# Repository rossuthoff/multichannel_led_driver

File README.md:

# multichannel_led_driver
Switching boost LED driver based on the Linear Technology [LT3478-1](http://www.analog.com/en/products/power-management/led-driver-ic/buck-boost-led-drivers/lt3478.html) chip.

## related repositories
This design requires the footprints found in the [kicad_footprints](https://github.com/rossuthoff/kicad_footprints) repository. Make sure the library and .mod files are added to your folder search locations. This board utilizes the [ytai/IOIO](https://github.com/ytai/ioio) microcontroller (MCU) and is designed to match to its header layout. Other microcontrollers that can send 3.3 V signals and control an I2C interface may be used. 

## general use
### power supply
LED driver is used in boost mode. The battery voltage must be less than the voltage drop across each individual LED string. Header connnection between this board and the IOIO board provide power to the MCU.

### led strings
Connect the LED strings to V+ (anode) and V1 through V9 (cathodes) connections. The LED string to be illuminated is controlled through a 3.3V signal to the s1 through s9 pins. The applied current is controlled through a Analog Devices [AD5247](http://www.analog.com/en/products/digital-to-analog-converters/digital-potentiometers/ad5247.html) digital potentiometer with an I2C interface.

# references

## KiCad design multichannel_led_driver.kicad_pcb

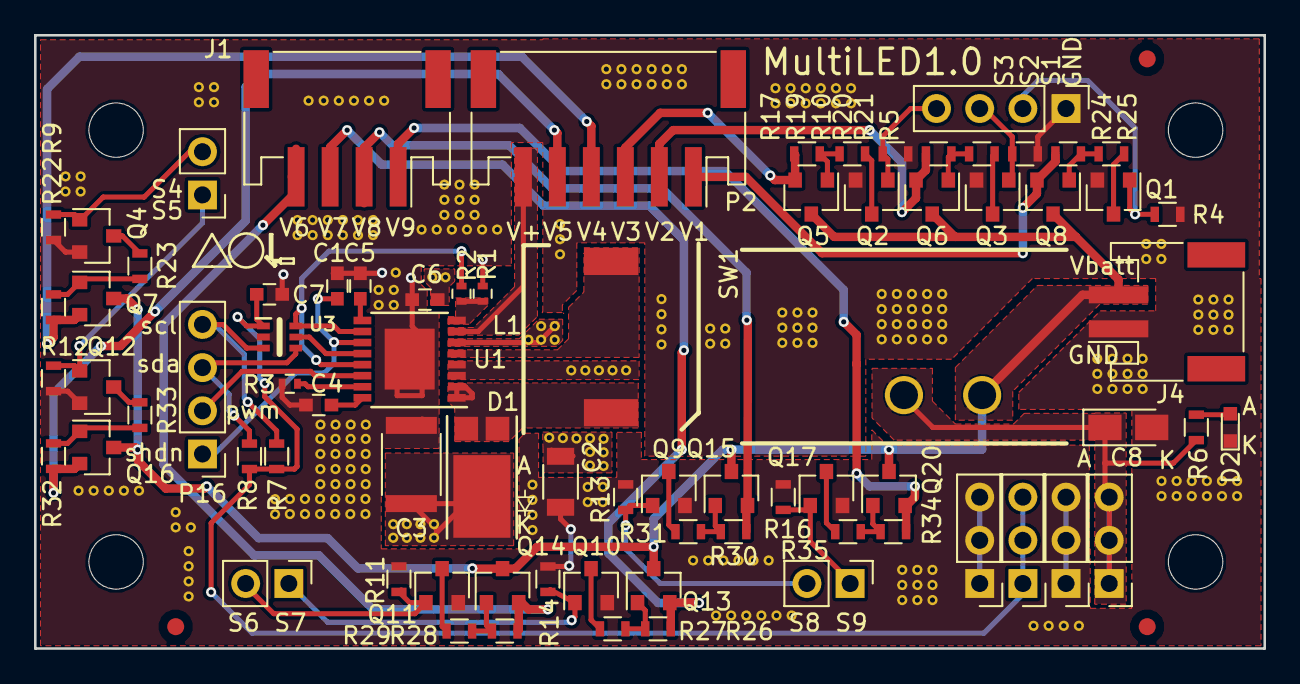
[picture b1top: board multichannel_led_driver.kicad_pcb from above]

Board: 2 copper layers, 72.3 x 36.1 mm, 69 parts (0 on the bottom side), 55 nets.

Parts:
C1: 3.3uF; C_0603
C2: 4.7uF; C_1206
C3: 10uF; C_1812
C4, C6: 1uF; C_0603
C5, C7: 0.1uF; C_0603
C8: 10u; CP_Tantalum_Case-A_EIA-3216-18_Reflow
D1: D_Schottky_AAK; D_PowerDI-5
D2: LED; LED_0603
J1: CONN_01X04; JST_PH_S4B-PH-SM4-TB_04x2.00mm_Angled
J4: CONN_01X02; JST_PH_S2B-PH-SM4-TB_02x2.00mm_Angled
L1: 6.8uH; Sumida_L_CDRH105R
P2: CONN_01X06; JST_PH_S6B-PH-SM4-TB_06x2.00mm_Angled
P16: CONN_01X04; Pin_Header_Straight_1x04_Pitch2.54mm
Q1, Q2, Q3, Q4, Q9, Q10, Q11, Q12, Q17: Si2312CDS; SOT-23
Q5, Q6, Q7, Q8, Q13, Q14, Q15, Q16, Q20: Si2315BDS; SOT-23
R1: 100k; R_0402
R2: 24k; R_0402
R3: 69.8k; R_0402
R4, R5, R7, R8, R9, R10, R11, R12, R13, R14, R16: 10k; R_0603
R6: 1k; R_0603
R17, R19, R20, R21, R22, R23, R24, R25, R26, R27, R28, R29, R30, R31, R32, R33, R34, R35: 510; R_0603
SW1: SW_SPST; C&K_SPST_switch_L101011MS02Q
U1: LT3478-1; TSSOP-16-1EP_4.4x5mm_Pitch0.65mm
U3: AD5247; SC-70-6

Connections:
/R_t: R3.2, U1.15
/S1: Q1.1, R4.1
/S2: Q3.1, R5.1
/S3: Q2.1, R10.1
/S4: Q4.1, R9.1
/S5: Q12.1, R12.1
/S6: Q11.1, R11.1
/S7: Q10.1, R14.1
/S8: Q9.1, R13.1
/S9: Q17.1, R16.1
/SCL: P16.4, R7.1, U3.3
/SDA: P16.3, R8.1, U3.4
/SHDN: C1.1, P16.1, U1.11
/SS: C4.1, U1.16
/SW: D1.1, D1.2, L1.1, U1.1, U1.2
/V1-: P2.1, Q8.2, R24.1
/V2-: P2.2, Q6.2, R20.1
/V3-: P2.3, Q5.2, R17.1
/V4-: P2.4, Q7.2, R22.1
/V5-: P2.5, Q16.2, R32.1
/V6-: J1.4, Q14.2, R28.1
/V7-: J1.3, Q13.2, R26.1
/V8-: J1.2, Q15.2, R30.1
/V9-: J1.1, Q20.2, R34.1
/V+: P2.6, U1.7
/V_batt: J4.2, Q5.3, Q6.3, Q7.3, Q8.3, Q13.3, Q14.3, Q15.3, Q16.3, Q20.3, SW1.1
/V_c: C5.1, U1.9
/V_dp: C7.1, R7.2, R8.2, U3.1
/V_io: C2.1, C6.1, C8.1, R6.2, SW1.2, U1.3, U1.4
/V_ref: R2.1, U1.10, U1.13, U3.6
/ctrl1: U1.12, U3.5
/induc: L1.2, U1.5
/ovpset: R1.1, R2.2, U1.8
/pwm: P16.2, U1.14
/v_out: C3.1, D1.3, U1.6
GND: C1.2, C2.2, C3.2, C4.2, C5.2, C6.2, C7.2, C8.2, D2.1, J4.1, Q1.2, Q2.2, Q3.2, Q4.2, Q9.2, Q10.2, Q11.2, Q12.2, Q17.2, R1.2, R3.1, R4.2, R5.2, R9.2, R10.2, R11.2, R12.2, R13.2, R14.2, R16.2, U1.17, U3.2
unnamed: D2.2, R6.1
unnamed: Q1.3, R25.2
unnamed: Q2.3, R19.2
unnamed: Q3.3, R21.2
unnamed: Q4.3, R23.2
unnamed: Q5.1, R17.2, R19.1
unnamed: Q6.1, R20.2, R21.1
unnamed: Q7.1, R22.2, R23.1
unnamed: Q8.1, R24.2, R25.1
unnamed: Q9.3, R31.2
unnamed: Q10.3, R27.2
unnamed: Q11.3, R29.2
unnamed: Q12.3, R33.2
unnamed: Q13.1, R26.2, R27.1
unnamed: Q14.1, R28.2, R29.1
unnamed: Q15.1, R30.2, R31.1
unnamed: Q16.1, R32.2, R33.1
unnamed: Q17.3, R35.2
unnamed: Q20.1, R34.2, R35.1
